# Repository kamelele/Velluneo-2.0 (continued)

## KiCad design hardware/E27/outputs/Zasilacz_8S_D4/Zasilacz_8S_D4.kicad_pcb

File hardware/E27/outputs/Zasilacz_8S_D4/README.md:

# Velluneo E27 8S-D4

Open [Zasilacz_8S_D4.kicad_pro](Zasilacz_8S_D4.kicad_pro) in KiCad 10.0.8. This draft adds a hardware inhibit to the 8-LED supply while its 3.3 V logic rail is low. The [70 × 34 mm board](Zasilacz_8S_D4.kicad_pcb) is an unrouted placement study.

- [Schematic](Zasilacz_8S_D4.kicad_sch)
- [3D top](8S-D4-top.png) · [3D bottom](8S-D4-bottom.png)
- [Design decision and evidence](../../workflow/8s/driver-8s-d4-inhibit.md)

Retained fault state after full rail loss, independent insulation checks and routing remain open. The earlier [D3 study](../Zasilacz_8S_Draft/README.md) is available as a baseline.

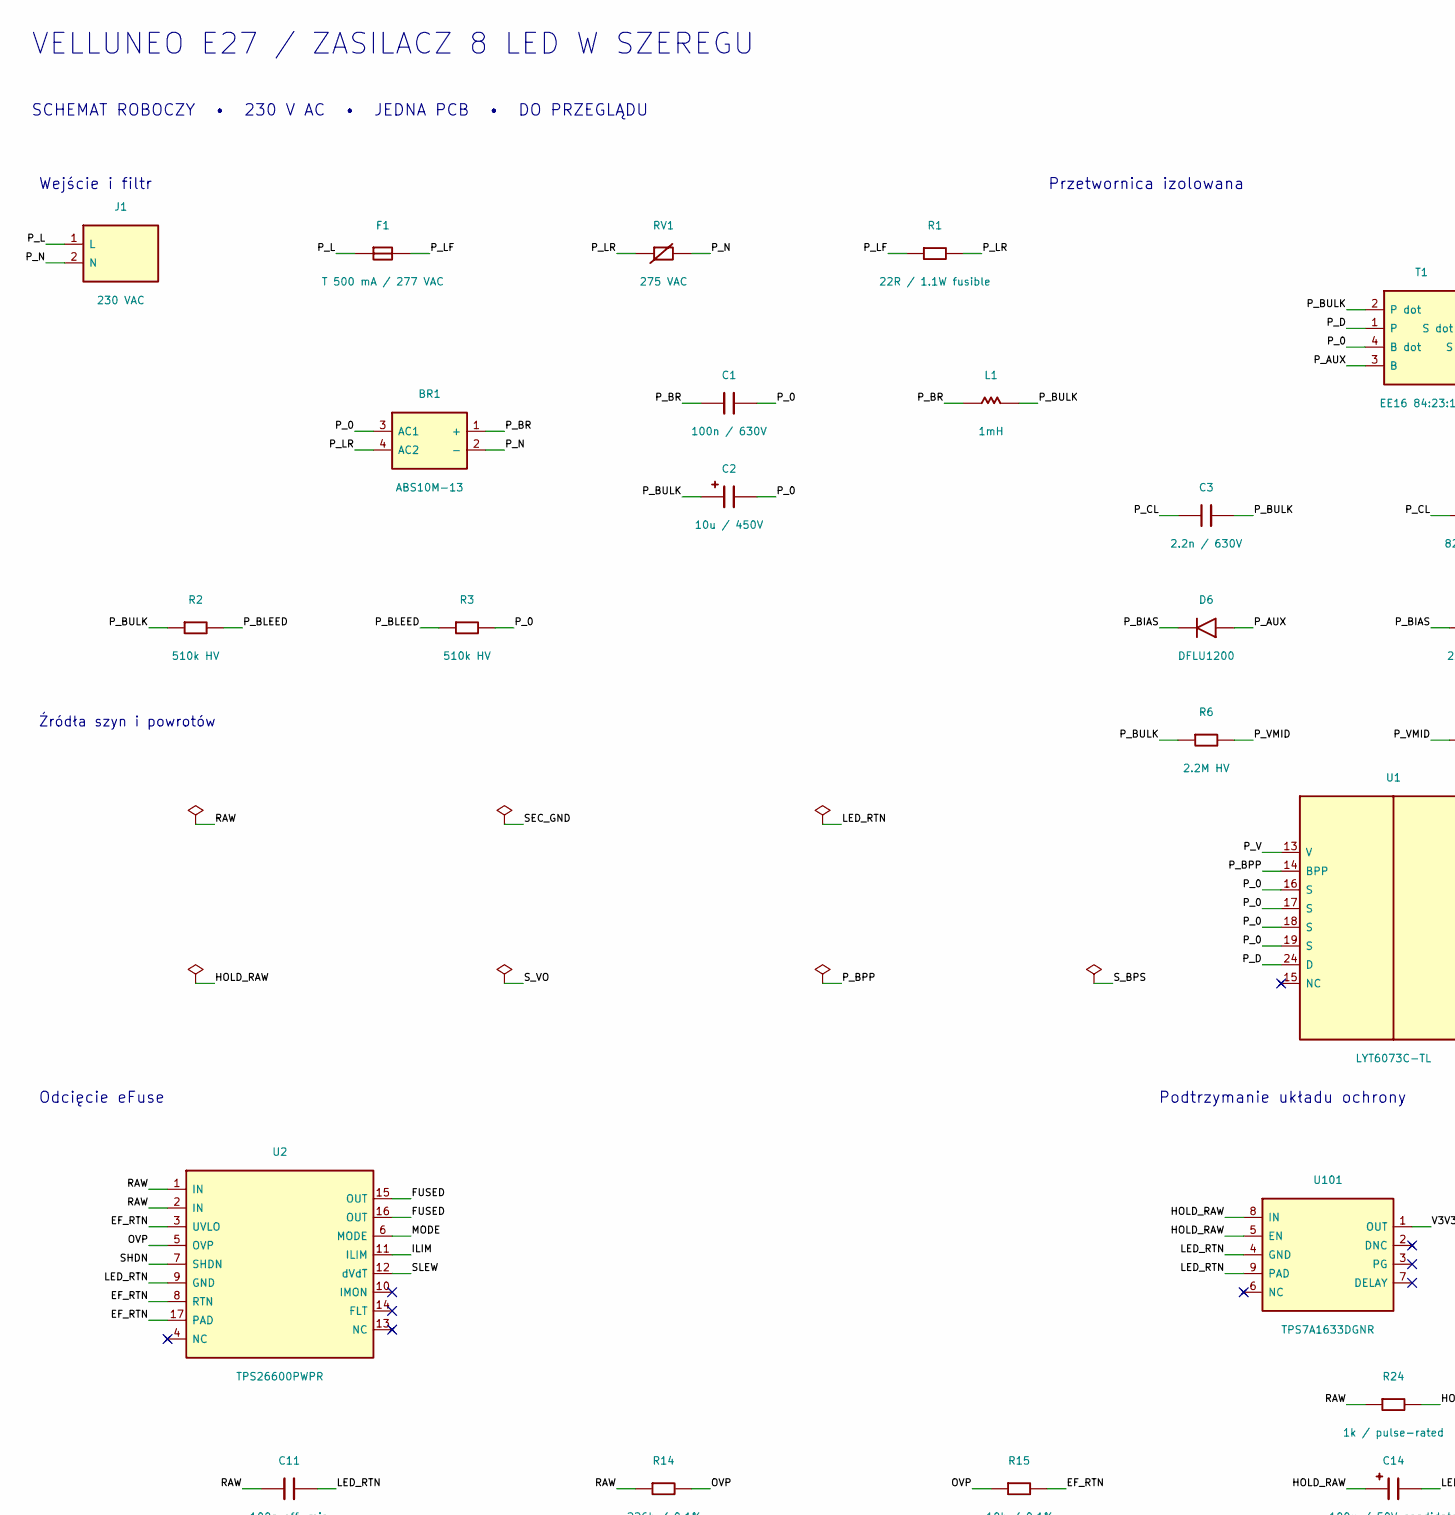
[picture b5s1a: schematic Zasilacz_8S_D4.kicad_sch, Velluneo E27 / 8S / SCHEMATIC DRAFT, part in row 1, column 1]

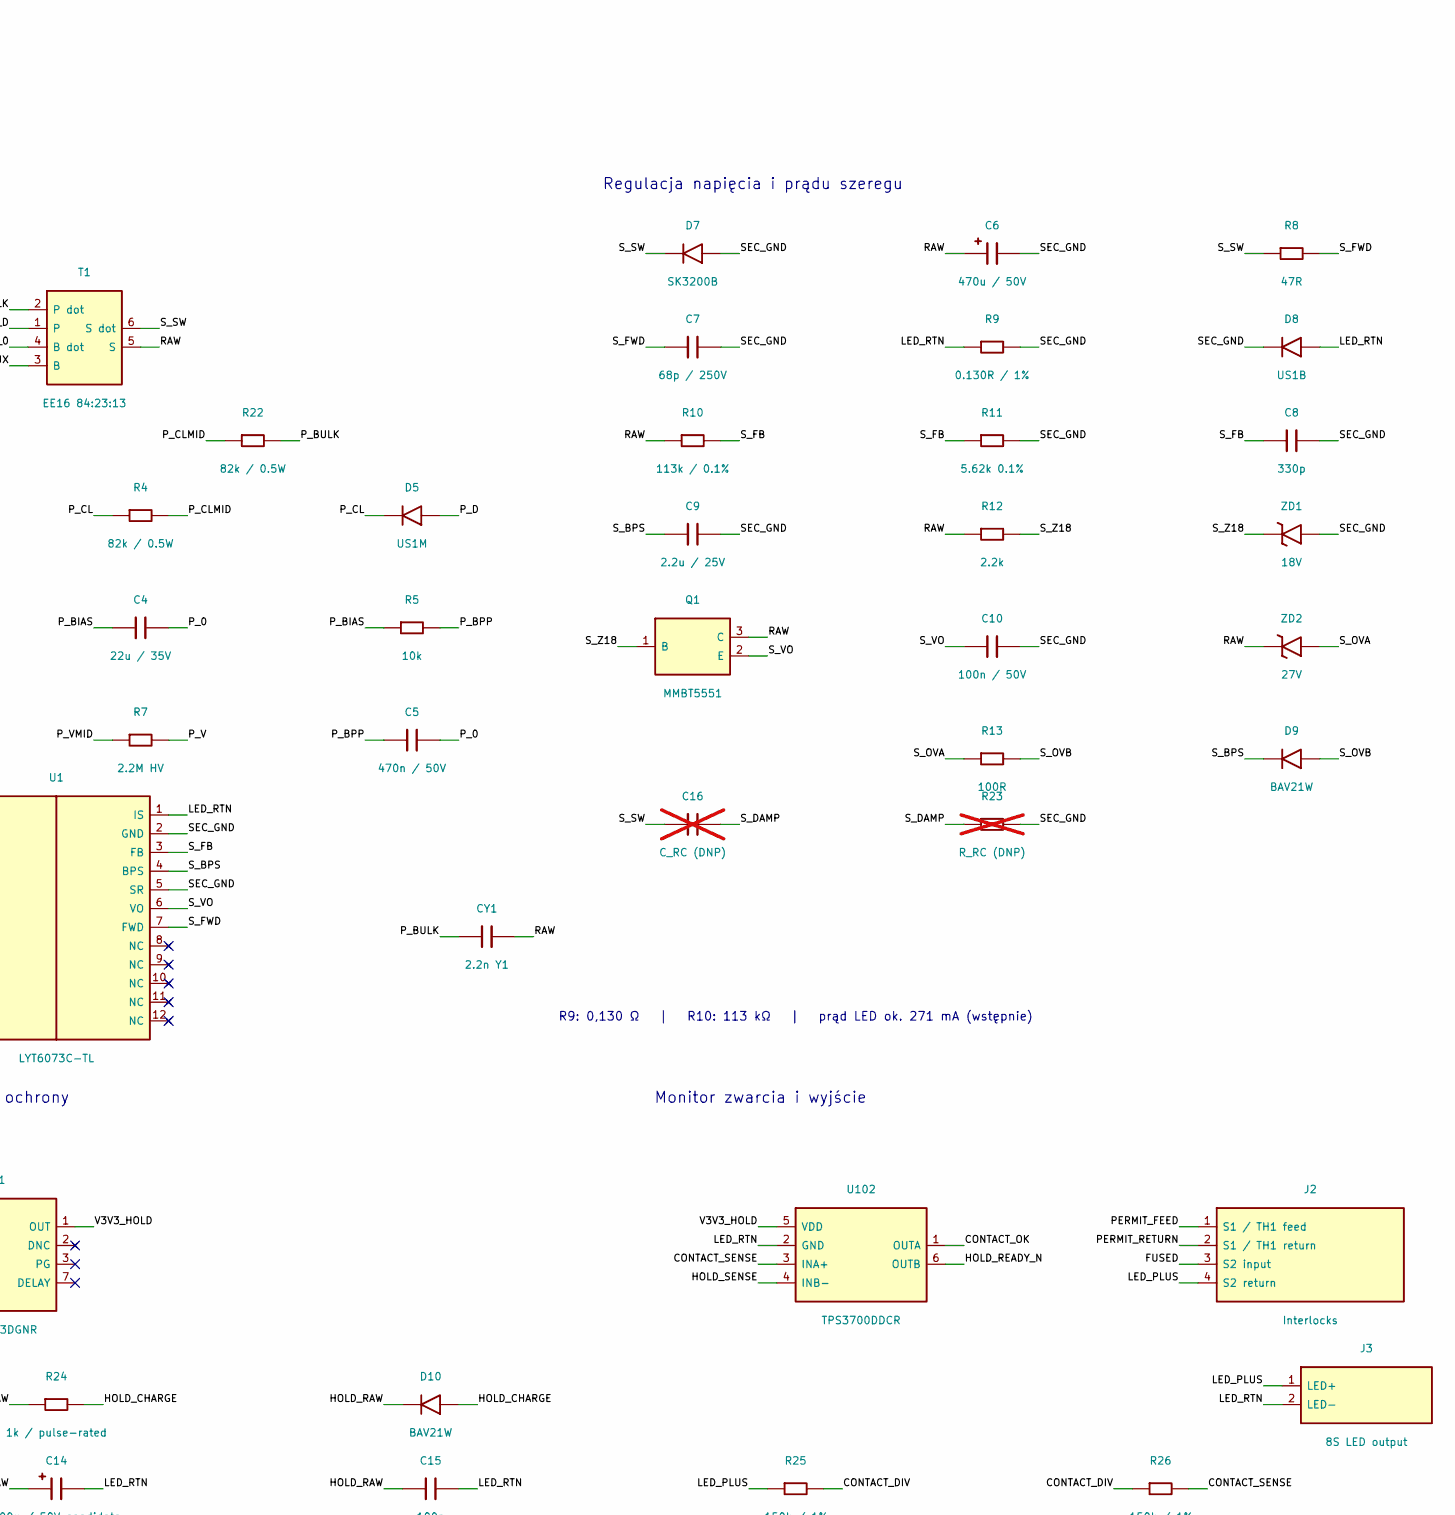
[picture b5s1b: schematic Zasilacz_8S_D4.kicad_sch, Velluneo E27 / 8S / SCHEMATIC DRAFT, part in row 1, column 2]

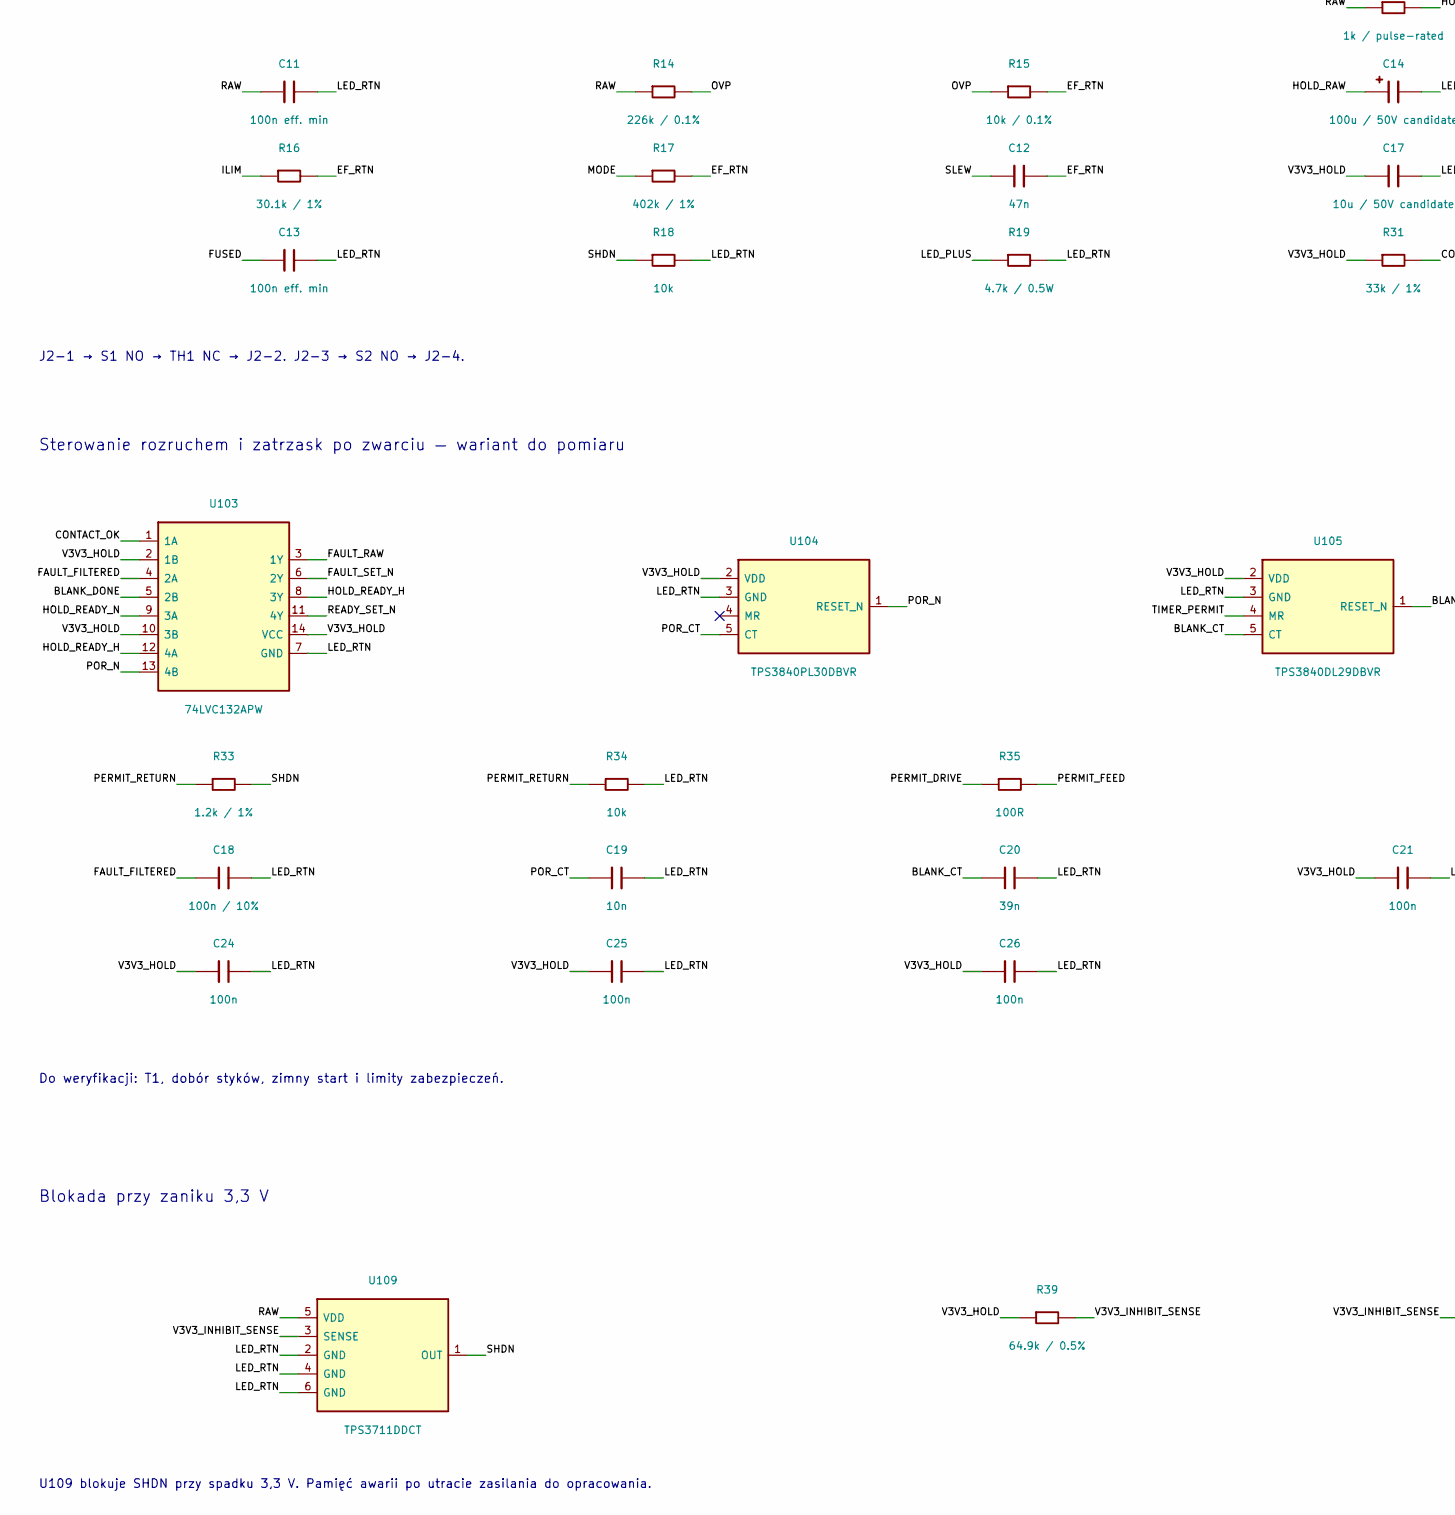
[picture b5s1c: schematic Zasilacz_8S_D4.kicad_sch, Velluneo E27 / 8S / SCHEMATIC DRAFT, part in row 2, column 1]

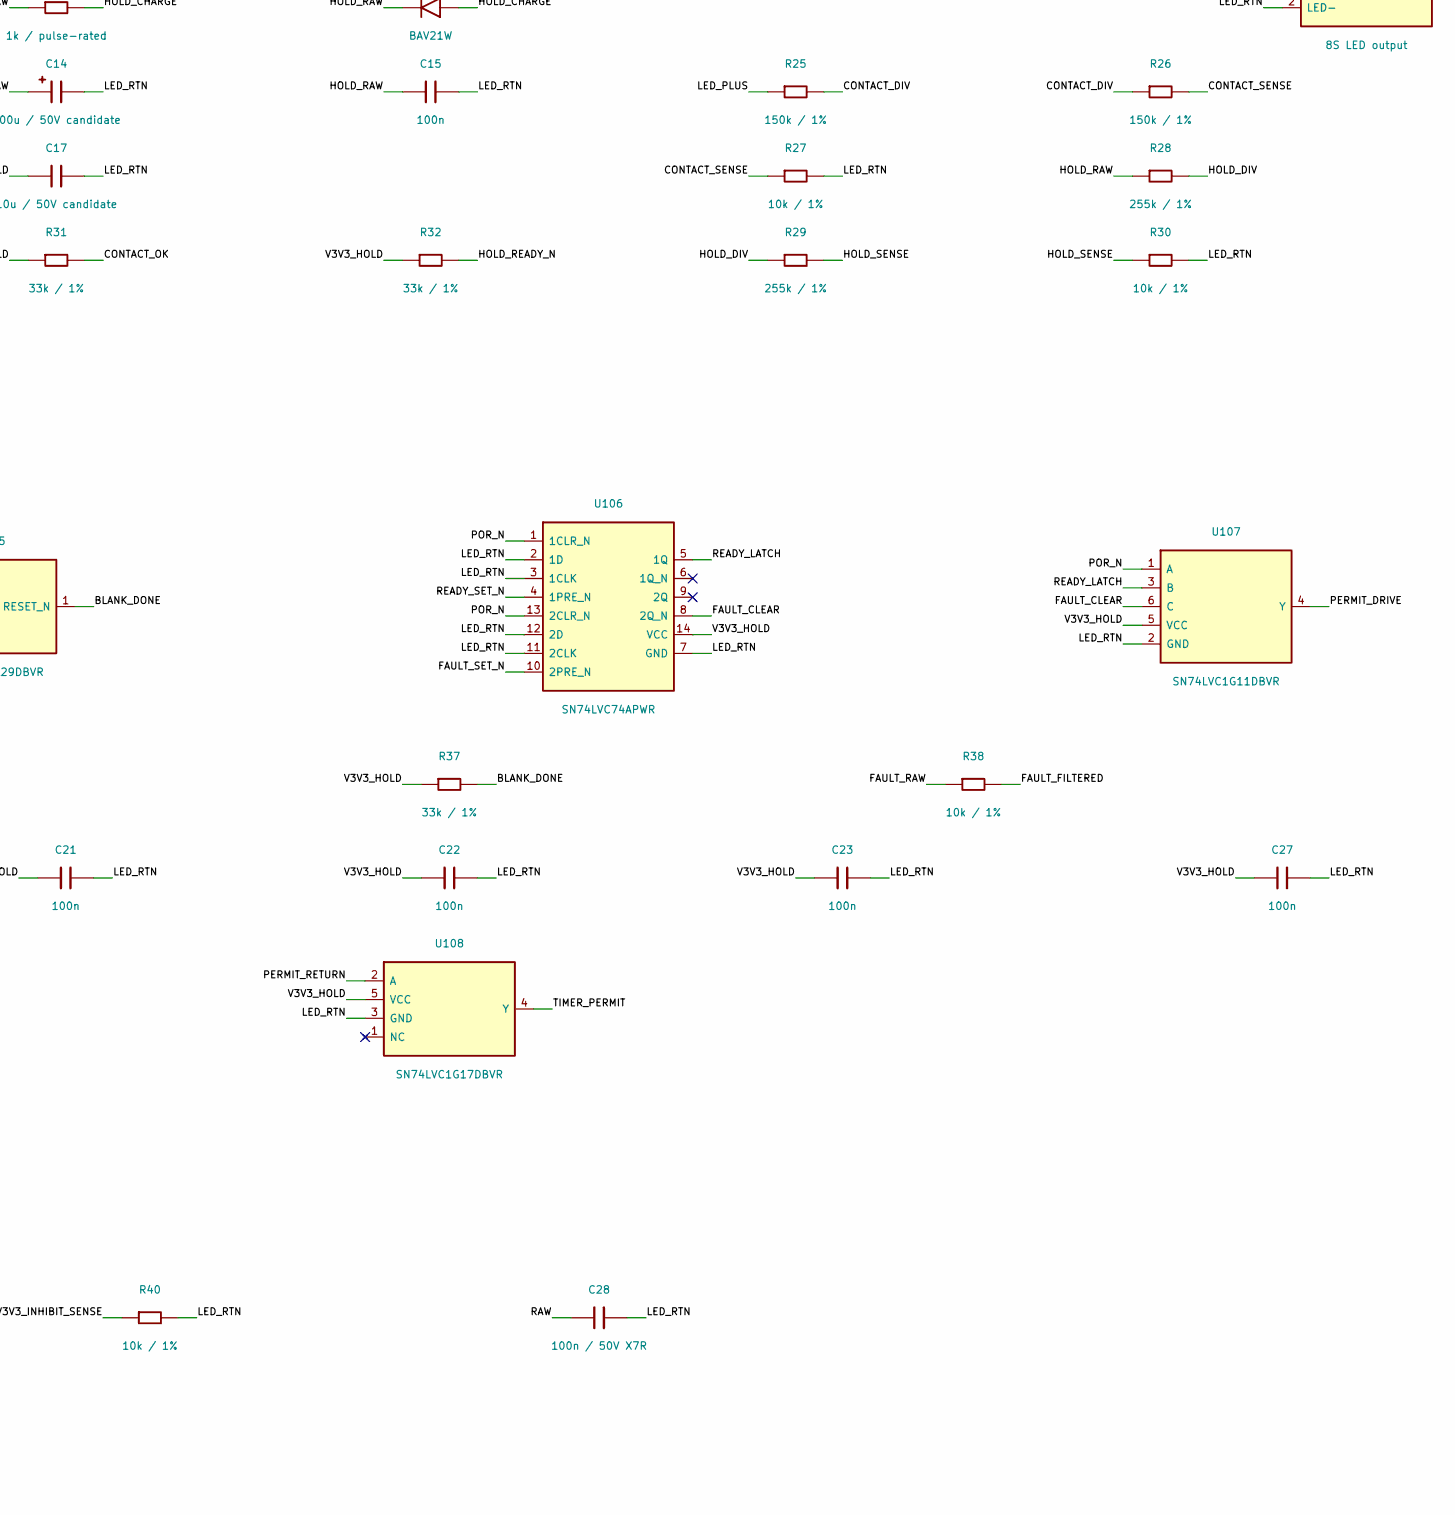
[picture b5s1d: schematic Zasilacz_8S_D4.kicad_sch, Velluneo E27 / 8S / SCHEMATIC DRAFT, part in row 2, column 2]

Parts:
BR1: ABS10M-13; ABS10M_SOPA-4_WX
C1: 100n / 630V; C_1210_3225Metric
C2: 10u / 450V; CP_Radial_D10.0mm_P5.00mm
C3: 2.2n / 630V; C_1206_3216Metric
C4: 22u / 35V; C_1206_3216Metric
C5: 470n / 50V; C_0805_2012Metric
C6: 470u / 50V; UCM_12p5
C7: 68p / 250V; C_0603_1608Metric
C8: 330p; C_0603_1608Metric
C9: 2.2u / 25V; C_1206_3216Metric
C10: 100n / 50V; C_0805_2012Metric
C11, C13: 100n eff. min; C_0805_2012Metric
C12: 47n; C_0603_1608Metric
C14: 100u / 50V candidate; CP_Elec_10x10.5
C15: 100n; C_0805_2012Metric
C16: C_RC (DNP); C_RC_1206_Hand; not fitted
C17: 10u / 50V candidate; C_1210_3225Metric
C18: 100n / 10%; C_0603_1608Metric
C19: 10n; C_0603_1608Metric
C20: 39n; C_0603_1608Metric
C21, C22, C23, C24, C25, C26, C27: 100n; C_0603_1608Metric
C28: 100n / 50V X7R; C_0805_2012Metric
CY1: 2.2n Y1; CY1_10mm
D5: US1M; D_SMA
D6: DFLU1200; D_PowerDI-123
D7: SK3200B; D_SMB
D8: US1B; D_SMA
D9, D10: BAV21W; D_SOD-123
F1: T 500 mA / 277 VAC; Schurter_UMT_H
J1: 230 VAC; Mains_L_N
J2: Interlocks; JST_GH_SM04B-GHS-TB_1x04-1MP_P1.25mm_Horizontal
J3: 8S LED output; JST_GH_SM02B-GHS-TB_1x02-1MP_P1.25mm_Horizontal
L1: 1mH; Wurth_TI_HV_8
Q1: MMBT5551; SOT-23
R1: 22R / 1.1W fusible; AC01_CS_WSZ
R2, R3: 510k HV; R_2010_5025Metric
R4, R22: 82k / 0.5W; R_1206_3216Metric
R5: 10k; R_0805_2012Metric
R6, R7: 2.2M HV; R_2010_5025Metric
R8: 47R; R_0805_2012Metric
R9: 0.130R / 1%; R_1206_3216Metric
R10: 113k / 0.1%; R_0603_1608Metric
R11: 5.62k 0.1%; R_0603_1608Metric
R12: 2.2k; R_0805_2012Metric
R13: 100R; R_0805_2012Metric
R14: 226k / 0.1%; R_0603_1608Metric
R15: 10k / 0.1%; R_0603_1608Metric
R16: 30.1k / 1%; R_0603_1608Metric
R17: 402k / 1%; R_0603_1608Metric
R18, R34: 10k; R_0603_1608Metric
R19: 4.7k / 0.5W; R_1206_3216Metric
R23: R_RC (DNP); R_RC_0805_Hand; not fitted
R24: 1k / pulse-rated; R_1206_3216Metric
R25, R26: 150k / 1%; R_0603_1608Metric
R27, R30, R38, R40: 10k / 1%; R_0603_1608Metric
R28, R29: 255k / 1%; R_0603_1608Metric
R31, R32, R37: 33k / 1%; R_0603_1608Metric
R33: 1.2k / 1%; R_0603_1608Metric
R35: 100R; R_0603_1608Metric
R39: 64.9k / 0.5%; R_0603_1608Metric
RV1: 275 VAC; TMOV14
T1: EE16 84:23:13; EE16_6pins_RFQ
U1: LYT6073C-TL; InSOP_24D
U2: TPS26600PWPR; PWP0016A
U101: TPS7A1633DGNR; TPS7A16_DGN
U102: TPS3700DDCR; SOT-23-6
U103: 74LVC132APW; TSSOP-14_4.4x5mm_P0.65mm
U104: TPS3840PL30DBVR; SOT-23-5
U105: TPS3840DL29DBVR; SOT-23-5
U106: SN74LVC74APWR; TSSOP-14_4.4x5mm_P0.65mm
U107: SN74LVC1G11DBVR; SOT-23-6
U108: SN74LVC1G17DBVR; SOT-23-5
U109: TPS3711DDCT; SOT-23-6
ZD1: 18V; D_SOD-123
ZD2: 27V; D_SOD-123

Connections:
/BLANK_CT: C20.1, U105.5 (CT)
/BLANK_DONE: R37.2, U103.5 (2B), U105.1 (RESET_N)
/CONTACT_DIV: R25.2, R26.1
/CONTACT_OK: R31.2, U102.1 (OUTA), U103.1 (1A)
/CONTACT_SENSE: R26.2, R27.1, U102.3 (INA+)
/EF_RTN: C12.2, R15.2, R16.2, R17.2, U2.3 (UVLO), U2.8 (RTN), U2.17 (PAD)
/FAULT_CLEAR: U106.8 (2Q_N), U107.6 (C)
/FAULT_FILTERED: C18.1, R38.2, U103.4 (2A)
/FAULT_RAW: R38.1, U103.3 (1Y)
/FAULT_SET_N: U103.6 (2Y), U106.10 (2PRE_N)
/FUSED: C13.1, J2.3 (S2 input), U2.15 (OUT), U2.16 (OUT)
/HOLD_CHARGE: D10.2 (A), R24.2
/HOLD_DIV: R28.2, R29.1
/HOLD_RAW: C14.1, C15.1, D10.1 (K), R28.1, U101.5 (EN), U101.8 (IN)
/HOLD_READY_H: U103.8 (3Y), U103.12 (4A)
/HOLD_READY_N: R32.2, U102.6 (OUTB), U103.9 (3A)
/HOLD_SENSE: R29.2, R30.1, U102.4 (INB-)
/ILIM: R16.1, U2.11 (ILIM)
/LED_PLUS: J2.4 (S2 return), J3.1 (LED+), R19.1, R25.1
/LED_RTN: C11.2, C13.2, C14.2, C15.2, C17.2, C18.2, C19.2, C20.2, C21.2, C22.2, C23.2, C24.2, C25.2, C26.2, C27.2, C28.2, D8.2 (A), J3.2 (LED-), R9.1, R18.2, R19.2, R27.2, R30.2, R34.2, R40.2, U1.1 (IS), U2.9 (GND), U101.4 (GND), U101.9 (PAD), U102.2 (GND), U103.7 (GND), U104.3 (GND), U105.3 (GND), U106.2 (1D), U106.3 (1CLK), U106.7 (GND), U106.11 (2CLK), U106.12 (2D), U107.2 (GND), U108.3 (GND), U109.2 (GND), U109.4 (GND), U109.6 (GND)
/MODE: R17.1, U2.6 (MODE)
/OVP: R14.2, R15.1, U2.5 (OVP)
/PERMIT_DRIVE: R35.1, U107.4 (Y)
/PERMIT_FEED: J2.1 (S1 / TH1 feed), R35.2
/PERMIT_RETURN: J2.2 (S1 / TH1 return), R33.1, R34.1, U108.2 (A)
/POR_CT: C19.1, U104.5 (CT)
/POR_N: U103.13 (4B), U104.1 (RESET_N), U106.1 (1CLR_N), U106.13 (2CLR_N), U107.1 (A)
/P_0: BR1.3 (AC1), C1.2, C2.2, C4.2, C5.2, R3.2, T1.4 (B dot), U1.16 (S), U1.17 (S), U1.18 (S), U1.19 (S)
/P_AUX: D6.2 (A), T1.3 (B)
/P_BIAS: C4.1, D6.1 (K), R5.1
/P_BLEED: R2.2, R3.1
/P_BPP: C5.1, R5.2, U1.14 (BPP)
/P_BR: BR1.1 (+), C1.1, L1.1
/P_BULK: C2.1, C3.2, CY1.1, L1.2, R2.1, R6.1, R22.2, T1.2 (P dot)
/P_CL: C3.1, D5.1 (K), R4.1
/P_CLMID: R4.2, R22.1
/P_D: D5.2 (A), T1.1, U1.24 (D)
/P_L: F1.1, J1.1 (L)
/P_LF: F1.2, R1.1
/P_LR: BR1.4 (AC2), R1.2, RV1.1
/P_N: BR1.2 (-), J1.2 (N), RV1.2
/P_V: R7.2, U1.13 (V)
/P_VMID: R6.2, R7.1
/RAW: C6.1, C11.1, C28.1, CY1.2, Q1.3 (C), R10.1, R12.1, R14.1, R24.1, T1.5 (S), U2.1 (IN), U2.2 (IN), U109.5 (VDD), ZD2.1 (K)
/READY_LATCH: U106.5 (1Q), U107.3 (B)
/READY_SET_N: U103.11 (4Y), U106.4 (1PRE_N)
/SEC_GND: C6.2, C7.2, C8.2, C9.2, C10.2, D7.2 (A), D8.1 (K), R9.2, R11.2, R23.2, U1.2 (GND), U1.5 (SR), ZD1.2 (A)
/SHDN: R18.1, R33.2, U2.7 (SHDN), U109.1 (OUT)
/SLEW: C12.1, U2.12 (dVdT)
/S_BPS: C9.1, D9.1 (K), U1.4 (BPS)
/S_DAMP: C16.2, R23.1
/S_FB: C8.1, R10.2, R11.1, U1.3 (FB)
/S_FWD: C7.1, R8.2, U1.7 (FWD)
/S_OVA: R13.1, ZD2.2 (A)
/S_OVB: D9.2 (A), R13.2
/S_SW: C16.1, D7.1 (K), R8.1, T1.6 (S dot)
/S_VO: C10.1, Q1.2 (E), U1.6 (VO)
/S_Z18: Q1.1 (B), R12.2, ZD1.1 (K)
/TIMER_PERMIT: U105.4 (MR), U108.4 (Y)
/V3V3_HOLD: C17.1, C21.1, C22.1, C23.1, C24.1, C25.1, C26.1, C27.1, R31.1, R32.1, R37.1, R39.1, U101.1 (OUT), U102.5 (VDD), U103.2 (1B), U103.10 (3B), U103.14 (VCC), U104.2 (VDD), U105.2 (VDD), U106.14 (VCC), U107.5 (VCC), U108.5 (VCC)
/V3V3_INHIBIT_SENSE: R39.2, R40.1, U109.3 (SENSE)

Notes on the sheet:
VELLUNEO E27 / ZASILACZ 8 LED W SZEREGU
SCHEMAT ROBOCZY • 230 V AC • JEDNA PCB • DO PRZEGLĄDU
Wejście i filtr
Przetwornica izolowana
Regulacja napięcia i prądu szeregu
R9: 0,130 Ω | R10: 113 kΩ | prąd LED ok. 271 mA (wstępnie)
Źródła szyn i powrotów
Odcięcie eFuse
Podtrzymanie układu ochrony
Monitor zwarcia i wyjście
J2-1 → S1 NO → TH1 NC → J2-2. J2-3 → S2 NO → J2-4.
Sterowanie rozruchem i zatrzask po zwarciu — wariant do pomiaru
Do weryfikacji: T1, dobór styków, zimny start i limity zabezpieczeń.
Blokada przy zaniku 3,3 V
U109 blokuje SHDN przy spadku 3,3 V. Pamięć awarii po utracie zasilania do opracowania.

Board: 2 copper layers, 94 parts (57 on the bottom side), 61 nets, no tracks yet.

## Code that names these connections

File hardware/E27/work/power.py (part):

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    add('C2','15u / 450V','Capacitor_THT:CP_Radial_D10.0mm_P5.00mm','P_BULK P_0',(17.6,12.5),(111.76,81.28),'CP',90,part='450BXF15M10X20',maker='Rubycon',function='Magazyn energii na szynie HV')
    add('R2','510k HV',R20,'P_BULK P_BLEED',(20.8,4.2),(39.37,99.06),'R',part='',function='Rozładowanie szyny HV',notes='Dwa rezystory szeregowe, potwierdzić napięcie pracy, dobrać tolerancję i udar.')
    add('R3','510k HV',R20,'P_BLEED P_0',(20.8,7.9),(76.2,99.06),'R',part='',function='Rozładowanie szyny HV')
    add('T1','EE16 84:23:13','E27:EE16_6pins_RFQ',{1:'P_D',2:'P_BULK',3:'P_AUX',4:'P_0',5:'S_RAW',6:'S_SW'},(BOUNDARY,9.6),(205.74,59.69),'T',part='',function='Transformator flyback 1.2 mH ±8%',notes='RFQ. Potwierdzić karkas, pinout, TIW, odstępy i badania. Zwroty w raporcie.')
    add('C3','1.5n / 200V',C80,'P_CL P_BULK',(24.1,20.2),(176.53,83.82),'C',90,part='08052C152KAT2A',maker='KYOCERA AVX',function='Kondensator ogranicznika RCD')
    add('R4','1M',R12,'P_CL P_BULK',(21.6,20.2),(213.36,83.82),'R',90,part='ERJ-8GEYJ105V',maker='Panasonic',function='Rezystor ogranicznika RCD')
    add('D5','US1J',SMA,'P_CL P_D',(25.25,16.75),(250.19,83.82),'D',part='US1J-13-F',maker='Diodes Inc.',function='Dioda ogranicznika RCD',notes='Potwierdzić impulsy, temperaturę i rzeczywiste VDS.')
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    add('C8','330p',C60,'S_FB S_GND',(43.3,27.75),(369.57,73.66),'C',part='CC0603KRX7R9BB331',maker='Yageo',function='Odprzęganie FB')
    add('C9','2.2u / 25V',C12,'S_BPS S_GND',(43.9,30.25),(288.29,86.36),'C',part='TMK316B7225KL-T',maker='Taiyo Yuden',function='Odprzęganie BPS')
    add('R12','2.2k',R80,'S_RAW S_Z18',(50.4,21.2),(328.93,86.36),'R',part='ERJ-6ENF2201V',maker='Panasonic',function='Prąd polaryzacji zenera VO')
    add('ZD1','18V',SOD,'S_Z18 S_GND',(54.2,23.5),(369.57,86.36),'Z',90,'BZT52C18-7-F','Diodes Inc.','Ograniczenie zasilania pinu VO')
    add('Q1','MMBT5551','Package_TO_SOT_SMD:SOT-23',{1:'S_Z18',2:'S_VO',3:'S_RAW'},(50.9,25.1),(288.29,101.6),'Q',part='MMBT5551LT1G',maker='onsemi',function='Wtórnik zasilający pin VO')
    add('C10','100n / 50V',C80,'S_VO S_GND',(47.5,25.65),(328.93,101.6),'C',90,'GRM21BR71H104KA01L','Murata','Odprzęganie VO')
    add('ZD2','27V',SOD,'S_RAW S_OVA',(52.6,29.4),(369.57,101.6),'Z',part='BZT52C27-7-F',maker='Diodes Inc.',function='Wtórne wykrywanie przepięcia')
    add('R13','100R',R80,'S_OVA S_OVB',(50.0,31.1),(328.93,116.84),'R',part='ERJ-6ENF1000V',maker='Panasonic',function='Ograniczenie prądu wstrzykiwanego do BPS')
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        left=[(3,'AC1'),(4,'AC2')]
        right=[(1,'+'),(2,'-')]
    else:
        labels={'AC':['L','N'],'J3':['A+','KA','KB'],'J4':['S1 feed','SHDN','eFuse out','LED A+']}[kind]
        left=list(enumerate(labels,1))
        right=[]
    half=10.16 if kind in ('LYT','EF') else 7.62 if kind=='J4' else 5.08
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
